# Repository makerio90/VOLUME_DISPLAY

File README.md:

# VOLUME_DISPLAY
this is a project i have been working on for the better part of a month now, this is only the first commit as i have dicided to add the project to github.

## The Idea:
i wanted to make a volumetric pov display. i got insperation from these projects:

- [this project is what kicked it off](https://hackaday.com/2024/09/09/doom-on-a-volumetric-display/)
- [and this served as insperation](https://hackaday.com/2021/02/21/volumetric-3d-television-is-here/)

both work off of the same principle: phisicly rotating an led matrix to create the sense of volume.

this seemed doable so i started work on schematics.

## theory of operation
cutting to the chase here: this is what the mainboard needs to do:

the main board is intended to drive a 32x16 led matrix at a high framerate (>1000fps).
new frames will be added to a framebuffer through a rs-485 bus. 12v power will also be supplied.
a hall effect sensor will provide a sync signal, allowing the board to make minor ajustments to its framerate.
most importently, this whole board rotates around. 12v and rs485 is fed through a slipring.

the entire board must be slowed to a stop in order for the rp2040 to be programmed.
whenever the usb port is plugged in. the rp2040 will be powered and in prog mode.
*the led drivers should be off when usb is plugged in!*

the board will be in the shape of a circle. the led matrix will be mounted vertically in the center via the attached pinheders.
because the board will likely be unbalanced, nuts and bolts will be added around in a circle to provide an option for balance.

## 4-layer stackup

top: high speed traces
in 1: signal, power & ground
in 2: Ground only
BOT: low speed, high current traces.

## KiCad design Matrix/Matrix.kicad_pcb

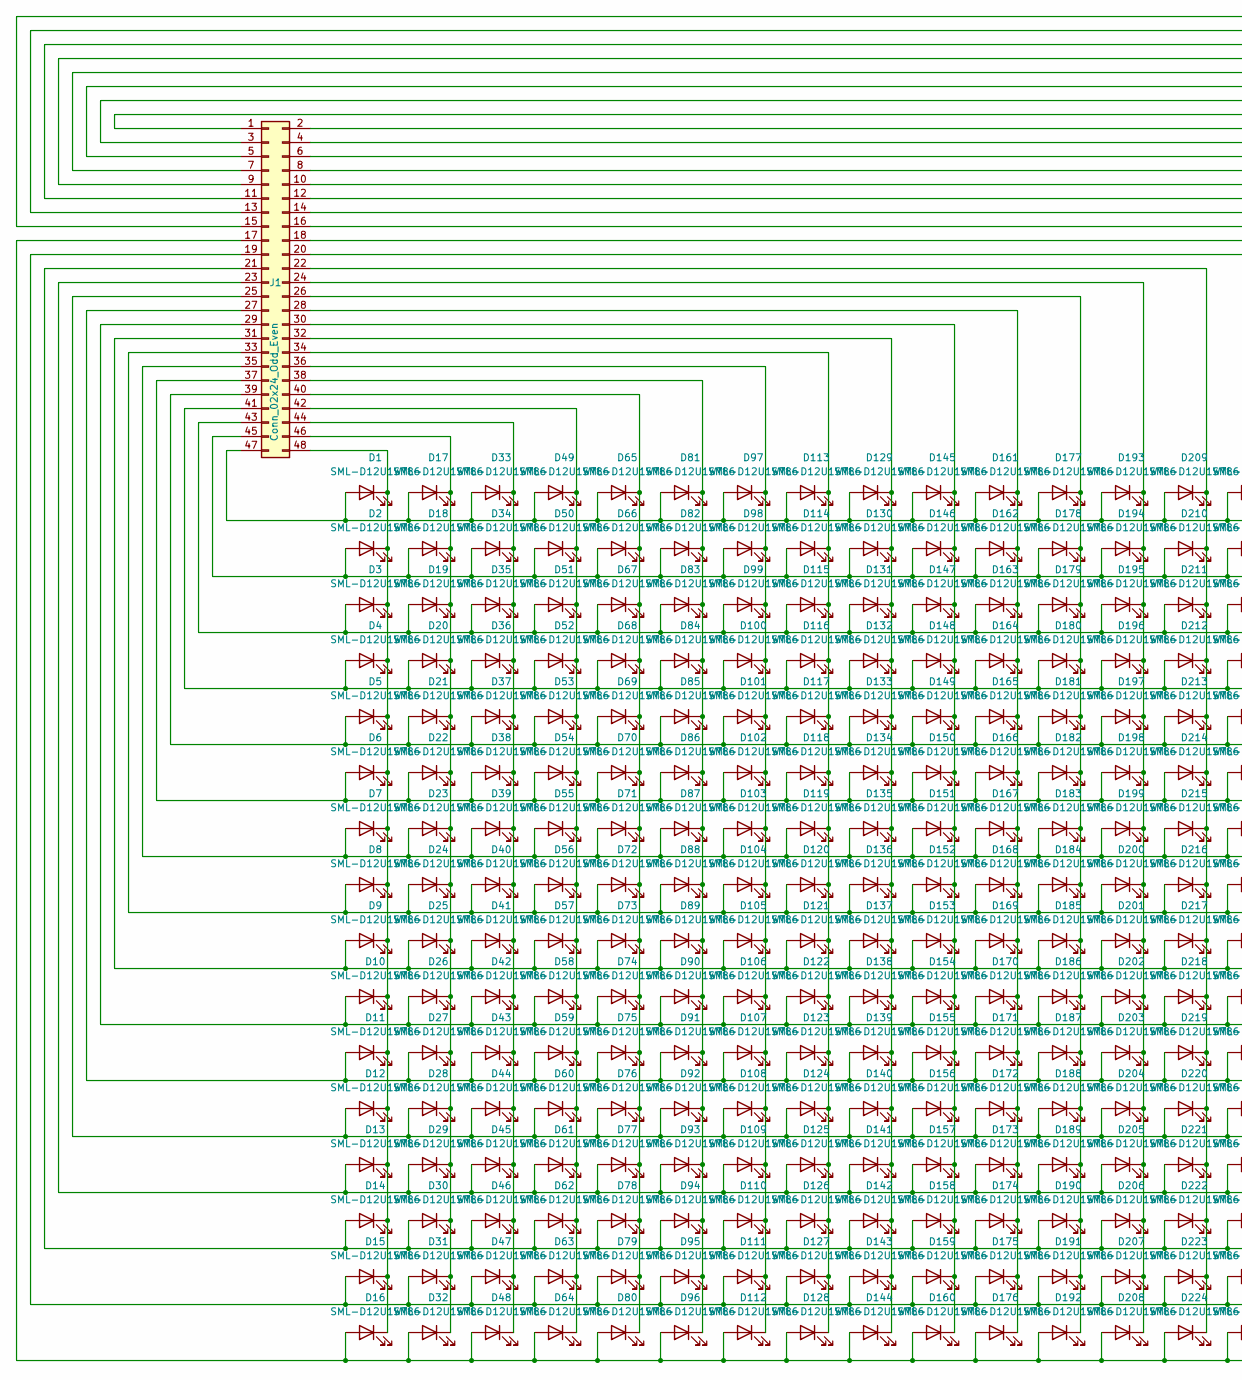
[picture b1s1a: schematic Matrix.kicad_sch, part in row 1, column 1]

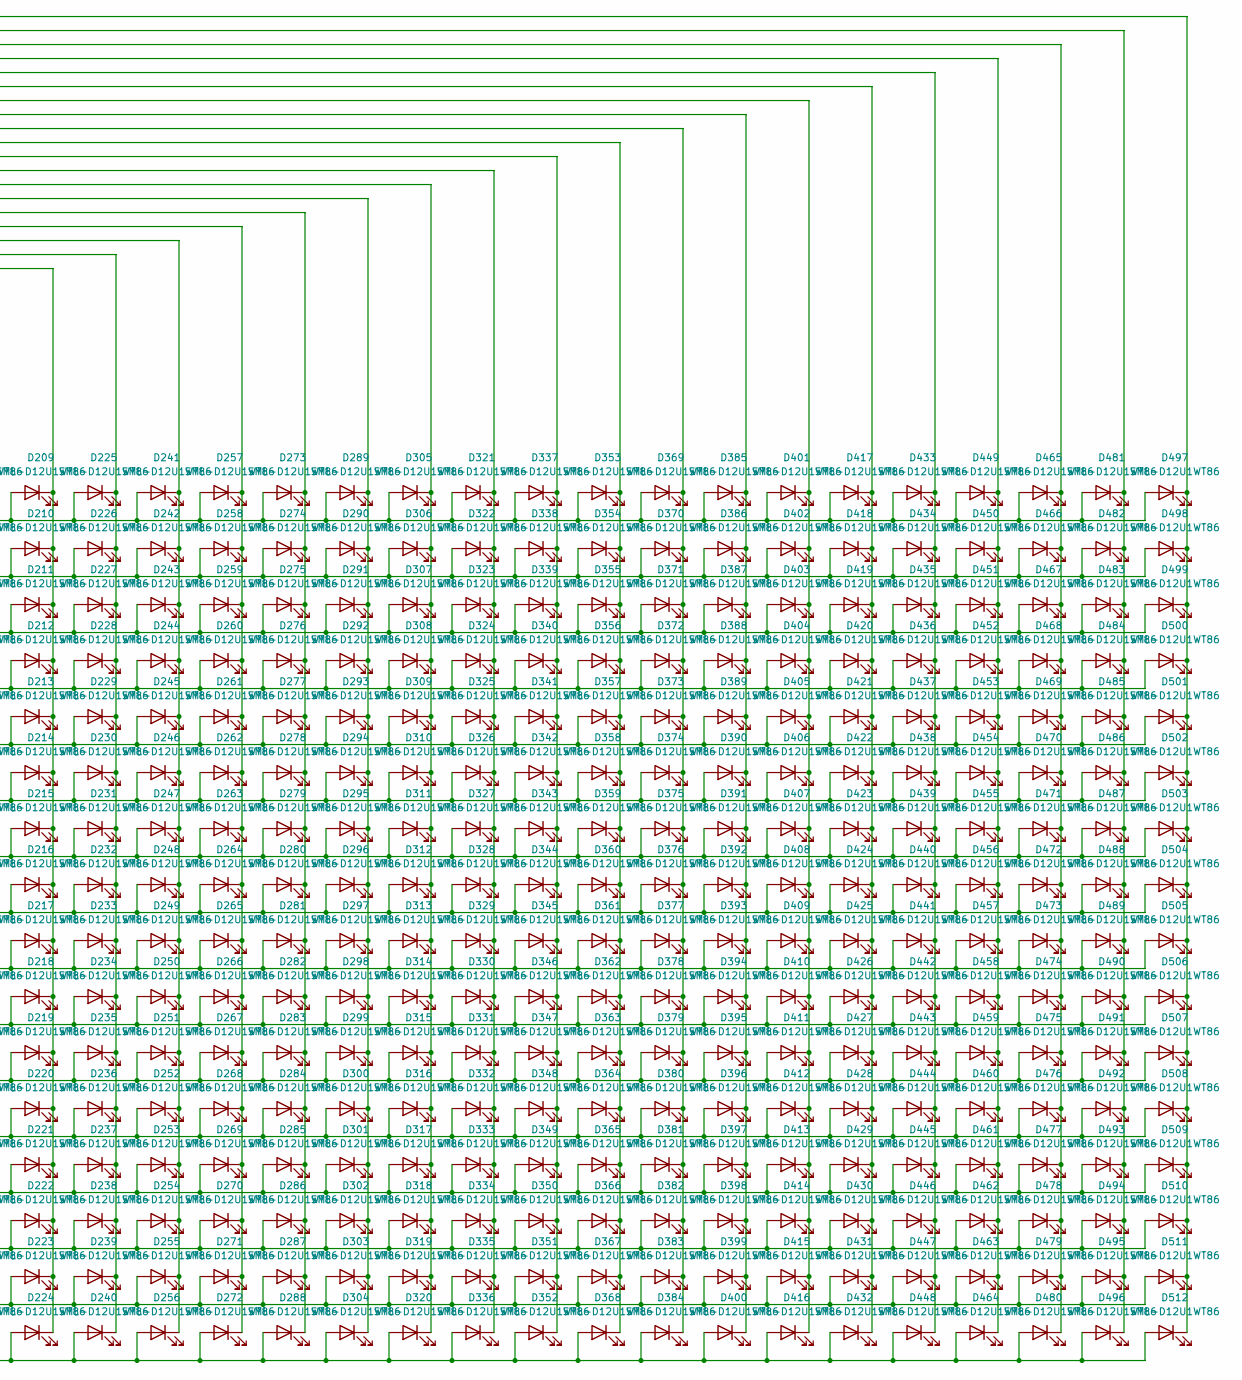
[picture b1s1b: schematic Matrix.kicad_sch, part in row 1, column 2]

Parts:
D1, D2, D3, D4, D5, D6, D7, D8, D9, D10, D11, D12, D13, D14, D15, D16, D17, D18, D19, D20, D21, D22, D23, D24, D25, D26, D27, D28, D29, D30, D31, D32, D33, D34, D35, D36, D37, D38, D39, D40, D41, D42, D43, D44, D45, D46, D47, D48, D49, D50, D51, D52, D53, D54, D55, D56, D57, D58, D59, D60, D61, D62, D63, D64, D65, D66, D67, D68, D69, D70, D71, D72, D73, D74, D75, D76, D77, D78, D79, D80, D81, D82, D83, D84, D85, D86, D87, D88, D89, D90, D91, D92, D93, D94, D95, D96, D97, D98, D99, D100, D101, D102, D103, D104, D105, D106, D107, D108, D109, D110, D111, D112, D113, D114, D115, D116, D117, D118, D119, D120, D121, D122, D123, D124, D125, D126, D127, D128, D129, D130, D131, D132, D133, D134, D135, D136, D137, D138, D139, D140, D141, D142, D143, D144, D145, D146, D147, D148, D149, D150, D151, D152, D153, D154, D155, D156, D157, D158, D159, D160, D161, D162, D163, D164, D165, D166, D167, D168, D169, D170, D171, D172, D173, D174, D175, D176, D177, D178, D179, D180, D181, D182, D183, D184, D185, D186, D187, D188, D189, D190, D191, D192, D193, D194, D195, D196, D197, D198, D199, D200, D201, D202, D203, D204, D205, D206, D207, D208, D209, D210, D211, D212, D213, D214, D215, D216, D217, D218, D219, D220, D221, D222, D223, D224, D225, D226, D227, D228, D229, D230, D231, D232, D233, D234, D235, D236, D237, D238, D239, D240, D241, D242, D243, D244, D245, D246, D247, D248, D249, D250, D251, D252, D253, D254, D255, D256, D257, D258, D259, D260, D261, D262, D263, D264, D265, D266, D267, D268, D269, D270, D271, D272, D273, D274, D275, D276, D277, D278, D279, D280, D281, D282, D283, D284, D285, D286, D287, D288, D289, D290, D291, D292, D293, D294, D295, D296, D297, D298, D299, D300, D301, D302, D303, D304, D305, D306, D307, D308, D309, D310, D311, D312, D313, D314, D315, D316, D317, D318, D319, D320, D321, D322, D323, D324, D325, D326, D327, D328, D329, D330, D331, D332, D333, D334, D335, D336, D337, D338, D339, D340, D341, D342, D343, D344, D345, D346, D347, D348, D349, D350, D351, D352, D353, D354, D355, D356, D357, D358, D359, D360, D361, D362, D363, D364, D365, D366, D367, D368, D369, D370, D371, D372, D373, D374, D375, D376, D377, D378, D379, D380, D381, D382, D383, D384, D385, D386, D387, D388, D389, D390, D391, D392, D393, D394, D395, D396, D397, D398, D399, D400, D401, D402, D403, D404, D405, D406, D407, D408, D409, D410, D411, D412, D413, D414, D415, D416, D417, D418, D419, D420, D421, D422, D423, D424, D425, D426, D427, D428, D429, D430, D431, D432, D433, D434, D435, D436, D437, D438, D439, D440, D441, D442, D443, D444, D445, D446, D447, D448, D449, D450, D451, D452, D453, D454, D455, D456, D457, D458, D459, D460, D461, D462, D463, D464, D465, D466, D467, D468, D469, D470, D471, D472, D473, D474, D475, D476, D477, D478, D479, D480, D481, D482, D483, D484, D485, D486, D487, D488, D489, D490, D491, D492, D493, D494, D495, D496, D497, D498, D499, D500, D501, D502, D503, D504, D505, D506, D507, D508, D509, D510, D511, D512: SML-D12U1WT86; LED_0603_1608Metric
J1: Conn_02x24_Odd_Even; PinHeader_2x24_P2.54mm_Horizontal

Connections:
unnamed: D1.2 (A), D17.2 (A), D33.2 (A), D49.2 (A), D65.2 (A), D81.2 (A), D97.2 (A), D113.2 (A), D129.2 (A), D145.2 (A), D161.2 (A), D177.2 (A), D193.2 (A), D209.2 (A), D225.2 (A), D241.2 (A), D257.2 (A), D273.2 (A), D289.2 (A), D305.2 (A), D321.2 (A), D337.2 (A), D353.2 (A), D369.2 (A), D385.2 (A), D401.2 (A), D417.2 (A), D433.2 (A), D449.2 (A), D465.2 (A), D481.2 (A), D497.2 (A), J1.47
unnamed: D1.1 (K), D2.1 (K), D3.1 (K), D4.1 (K), D5.1 (K), D6.1 (K), D7.1 (K), D8.1 (K), D9.1 (K), D10.1 (K), D11.1 (K), D12.1 (K), D13.1 (K), D14.1 (K), D15.1 (K), D16.1 (K), J1.48
unnamed: D10.2 (A), D26.2 (A), D42.2 (A), D58.2 (A), D74.2 (A), D90.2 (A), D106.2 (A), D122.2 (A), D138.2 (A), D154.2 (A), D170.2 (A), D186.2 (A), D202.2 (A), D218.2 (A), D234.2 (A), D250.2 (A), D266.2 (A), D282.2 (A), D298.2 (A), D314.2 (A), D330.2 (A), D346.2 (A), D362.2 (A), D378.2 (A), D394.2 (A), D410.2 (A), D426.2 (A), D442.2 (A), D458.2 (A), D474.2 (A), D490.2 (A), D506.2 (A), J1.29
unnamed: D17.1 (K), D18.1 (K), D19.1 (K), D20.1 (K), D21.1 (K), D22.1 (K), D23.1 (K), D24.1 (K), D25.1 (K), D26.1 (K), D27.1 (K), D28.1 (K), D29.1 (K), D30.1 (K), D31.1 (K), D32.1 (K), J1.46
unnamed: D33.1 (K), D34.1 (K), D35.1 (K), D36.1 (K), D37.1 (K), D38.1 (K), D39.1 (K), D40.1 (K), D41.1 (K), D42.1 (K), D43.1 (K), D44.1 (K), D45.1 (K), D46.1 (K), D47.1 (K), D48.1 (K), J1.44
unnamed: D49.1 (K), D50.1 (K), D51.1 (K), D52.1 (K), D53.1 (K), D54.1 (K), D55.1 (K), D56.1 (K), D57.1 (K), D58.1 (K), D59.1 (K), D60.1 (K), D61.1 (K), D62.1 (K), D63.1 (K), D64.1 (K), J1.42
unnamed: D65.1 (K), D66.1 (K), D67.1 (K), D68.1 (K), D69.1 (K), D70.1 (K), D71.1 (K), D72.1 (K), D73.1 (K), D74.1 (K), D75.1 (K), D76.1 (K), D77.1 (K), D78.1 (K), D79.1 (K), D80.1 (K), J1.40
unnamed: D81.1 (K), D82.1 (K), D83.1 (K), D84.1 (K), D85.1 (K), D86.1 (K), D87.1 (K), D88.1 (K), D89.1 (K), D90.1 (K), D91.1 (K), D92.1 (K), D93.1 (K), D94.1 (K), D95.1 (K), D96.1 (K), J1.38
unnamed: D4.2 (A), D20.2 (A), D36.2 (A), D52.2 (A), D68.2 (A), D84.2 (A), D100.2 (A), D116.2 (A), D132.2 (A), D148.2 (A), D164.2 (A), D180.2 (A), D196.2 (A), D212.2 (A), D228.2 (A), D244.2 (A), D260.2 (A), D276.2 (A), D292.2 (A), D308.2 (A), D324.2 (A), D340.2 (A), D356.2 (A), D372.2 (A), D388.2 (A), D404.2 (A), D420.2 (A), D436.2 (A), D452.2 (A), D468.2 (A), D484.2 (A), D500.2 (A), J1.41
unnamed: D97.1 (K), D98.1 (K), D99.1 (K), D100.1 (K), D101.1 (K), D102.1 (K), D103.1 (K), D104.1 (K), D105.1 (K), D106.1 (K), D107.1 (K), D108.1 (K), D109.1 (K), D110.1 (K), D111.1 (K), D112.1 (K), J1.36
unnamed: D5.2 (A), D21.2 (A), D37.2 (A), D53.2 (A), D69.2 (A), D85.2 (A), D101.2 (A), D117.2 (A), D133.2 (A), D149.2 (A), D165.2 (A), D181.2 (A), D197.2 (A), D213.2 (A), D229.2 (A), D245.2 (A), D261.2 (A), D277.2 (A), D293.2 (A), D309.2 (A), D325.2 (A), D341.2 (A), D357.2 (A), D373.2 (A), D389.2 (A), D405.2 (A), D421.2 (A), D437.2 (A), D453.2 (A), D469.2 (A), D485.2 (A), D501.2 (A), J1.39
unnamed: D6.2 (A), D22.2 (A), D38.2 (A), D54.2 (A), D70.2 (A), D86.2 (A), D102.2 (A), D118.2 (A), D134.2 (A), D150.2 (A), D166.2 (A), D182.2 (A), D198.2 (A), D214.2 (A), D230.2 (A), D246.2 (A), D262.2 (A), D278.2 (A), D294.2 (A), D310.2 (A), D326.2 (A), D342.2 (A), D358.2 (A), D374.2 (A), D390.2 (A), D406.2 (A), D422.2 (A), D438.2 (A), D454.2 (A), D470.2 (A), D486.2 (A), D502.2 (A), J1.37
unnamed: D7.2 (A), D23.2 (A), D39.2 (A), D55.2 (A), D71.2 (A), D87.2 (A), D103.2 (A), D119.2 (A), D135.2 (A), D151.2 (A), D167.2 (A), D183.2 (A), D199.2 (A), D215.2 (A), D231.2 (A), D247.2 (A), D263.2 (A), D279.2 (A), D295.2 (A), D311.2 (A), D327.2 (A), D343.2 (A), D359.2 (A), D375.2 (A), D391.2 (A), D407.2 (A), D423.2 (A), D439.2 (A), D455.2 (A), D471.2 (A), D487.2 (A), D503.2 (A), J1.35
unnamed: D8.2 (A), D24.2 (A), D40.2 (A), D56.2 (A), D72.2 (A), D88.2 (A), D104.2 (A), D120.2 (A), D136.2 (A), D152.2 (A), D168.2 (A), D184.2 (A), D200.2 (A), D216.2 (A), D232.2 (A), D248.2 (A), D264.2 (A), D280.2 (A), D296.2 (A), D312.2 (A), D328.2 (A), D344.2 (A), D360.2 (A), D376.2 (A), D392.2 (A), D408.2 (A), D424.2 (A), D440.2 (A), D456.2 (A), D472.2 (A), D488.2 (A), D504.2 (A), J1.33
unnamed: D9.2 (A), D25.2 (A), D41.2 (A), D57.2 (A), D73.2 (A), D89.2 (A), D105.2 (A), D121.2 (A), D137.2 (A), D153.2 (A), D169.2 (A), D185.2 (A), D201.2 (A), D217.2 (A), D233.2 (A), D249.2 (A), D265.2 (A), D281.2 (A), D297.2 (A), D313.2 (A), D329.2 (A), D345.2 (A), D361.2 (A), D377.2 (A), D393.2 (A), D409.2 (A), D425.2 (A), D441.2 (A), D457.2 (A), D473.2 (A), D489.2 (A), D505.2 (A), J1.31
unnamed: D11.2 (A), D27.2 (A), D43.2 (A), D59.2 (A), D75.2 (A), D91.2 (A), D107.2 (A), D123.2 (A), D139.2 (A), D155.2 (A), D171.2 (A), D187.2 (A), D203.2 (A), D219.2 (A), D235.2 (A), D251.2 (A), D267.2 (A), D283.2 (A), D299.2 (A), D315.2 (A), D331.2 (A), D347.2 (A), D363.2 (A), D379.2 (A), D395.2 (A), D411.2 (A), D427.2 (A), D443.2 (A), D459.2 (A), D475.2 (A), D491.2 (A), D507.2 (A), J1.27
unnamed: D12.2 (A), D28.2 (A), D44.2 (A), D60.2 (A), D76.2 (A), D92.2 (A), D108.2 (A), D124.2 (A), D140.2 (A), D156.2 (A), D172.2 (A), D188.2 (A), D204.2 (A), D220.2 (A), D236.2 (A), D252.2 (A), D268.2 (A), D284.2 (A), D300.2 (A), D316.2 (A), D332.2 (A), D348.2 (A), D364.2 (A), D380.2 (A), D396.2 (A), D412.2 (A), D428.2 (A), D444.2 (A), D460.2 (A), D476.2 (A), D492.2 (A), D508.2 (A), J1.25
unnamed: D13.2 (A), D29.2 (A), D45.2 (A), D61.2 (A), D77.2 (A), D93.2 (A), D109.2 (A), D125.2 (A), D141.2 (A), D157.2 (A), D173.2 (A), D189.2 (A), D205.2 (A), D221.2 (A), D237.2 (A), D253.2 (A), D269.2 (A), D285.2 (A), D301.2 (A), D317.2 (A), D333.2 (A), D349.2 (A), D365.2 (A), D381.2 (A), D397.2 (A), D413.2 (A), D429.2 (A), D445.2 (A), D461.2 (A), D477.2 (A), D493.2 (A), D509.2 (A), J1.23
unnamed: D14.2 (A), D30.2 (A), D46.2 (A), D62.2 (A), D78.2 (A), D94.2 (A), D110.2 (A), D126.2 (A), D142.2 (A), D158.2 (A), D174.2 (A), D190.2 (A), D206.2 (A), D222.2 (A), D238.2 (A), D254.2 (A), D270.2 (A), D286.2 (A), D302.2 (A), D318.2 (A), D334.2 (A), D350.2 (A), D366.2 (A), D382.2 (A), D398.2 (A), D414.2 (A), D430.2 (A), D446.2 (A), D462.2 (A), D478.2 (A), D494.2 (A), D510.2 (A), J1.21
unnamed: D15.2 (A), D31.2 (A), D47.2 (A), D63.2 (A), D79.2 (A), D95.2 (A), D111.2 (A), D127.2 (A), D143.2 (A), D159.2 (A), D175.2 (A), D191.2 (A), D207.2 (A), D223.2 (A), D239.2 (A), D255.2 (A), D271.2 (A), D287.2 (A), D303.2 (A), D319.2 (A), D335.2 (A), D351.2 (A), D367.2 (A), D383.2 (A), D399.2 (A), D415.2 (A), D431.2 (A), D447.2 (A), D463.2 (A), D479.2 (A), D495.2 (A), D511.2 (A), J1.19
unnamed: D16.2 (A), D32.2 (A), D48.2 (A), D64.2 (A), D80.2 (A), D96.2 (A), D112.2 (A), D128.2 (A), D144.2 (A), D160.2 (A), D176.2 (A), D192.2 (A), D208.2 (A), D224.2 (A), D240.2 (A), D256.2 (A), D272.2 (A), D288.2 (A), D304.2 (A), D320.2 (A), D336.2 (A), D352.2 (A), D368.2 (A), D384.2 (A), D400.2 (A), D416.2 (A), D432.2 (A), D448.2 (A), D464.2 (A), D480.2 (A), D496.2 (A), D512.2 (A), J1.17
unnamed: D113.1 (K), D114.1 (K), D115.1 (K), D116.1 (K), D117.1 (K), D118.1 (K), D119.1 (K), D120.1 (K), D121.1 (K), D122.1 (K), D123.1 (K), D124.1 (K), D125.1 (K), D126.1 (K), D127.1 (K), D128.1 (K), J1.34
unnamed: D2.2 (A), D18.2 (A), D34.2 (A), D50.2 (A), D66.2 (A), D82.2 (A), D98.2 (A), D114.2 (A), D130.2 (A), D146.2 (A), D162.2 (A), D178.2 (A), D194.2 (A), D210.2 (A), D226.2 (A), D242.2 (A), D258.2 (A), D274.2 (A), D290.2 (A), D306.2 (A), D322.2 (A), D338.2 (A), D354.2 (A), D370.2 (A), D386.2 (A), D402.2 (A), D418.2 (A), D434.2 (A), D450.2 (A), D466.2 (A), D482.2 (A), D498.2 (A), J1.45
unnamed: D3.2 (A), D19.2 (A), D35.2 (A), D51.2 (A), D67.2 (A), D83.2 (A), D99.2 (A), D115.2 (A), D131.2 (A), D147.2 (A), D163.2 (A), D179.2 (A), D195.2 (A), D211.2 (A), D227.2 (A), D243.2 (A), D259.2 (A), D275.2 (A), D291.2 (A), D307.2 (A), D323.2 (A), D339.2 (A), D355.2 (A), D371.2 (A), D387.2 (A), D403.2 (A), D419.2 (A), D435.2 (A), D451.2 (A), D467.2 (A), D483.2 (A), D499.2 (A), J1.43
unnamed: D129.1 (K), D130.1 (K), D131.1 (K), D132.1 (K), D133.1 (K), D134.1 (K), D135.1 (K), D136.1 (K), D137.1 (K), D138.1 (K), D139.1 (K), D140.1 (K), D141.1 (K), D142.1 (K), D143.1 (K), D144.1 (K), J1.32
unnamed: D145.1 (K), D146.1 (K), D147.1 (K), D148.1 (K), D149.1 (K), D150.1 (K), D151.1 (K), D152.1 (K), D153.1 (K), D154.1 (K), D155.1 (K), D156.1 (K), D157.1 (K), D158.1 (K), D159.1 (K), D160.1 (K), J1.30
unnamed: D161.1 (K), D162.1 (K), D163.1 (K), D164.1 (K), D165.1 (K), D166.1 (K), D167.1 (K), D168.1 (K), D169.1 (K), D170.1 (K), D171.1 (K), D172.1 (K), D173.1 (K), D174.1 (K), D175.1 (K), D176.1 (K), J1.28
unnamed: D177.1 (K), D178.1 (K), D179.1 (K), D180.1 (K), D181.1 (K), D182.1 (K), D183.1 (K), D184.1 (K), D185.1 (K), D186.1 (K), D187.1 (K), D188.1 (K), D189.1 (K), D190.1 (K), D191.1 (K), D192.1 (K), J1.26
unnamed: D193.1 (K), D194.1 (K), D195.1 (K), D196.1 (K), D197.1 (K), D198.1 (K), D199.1 (K), D200.1 (K), D201.1 (K), D202.1 (K), D203.1 (K), D204.1 (K), D205.1 (K), D206.1 (K), D207.1 (K), D208.1 (K), J1.24
unnamed: D209.1 (K), D210.1 (K), D211.1 (K), D212.1 (K), D213.1 (K), D214.1 (K), D215.1 (K), D216.1 (K), D217.1 (K), D218.1 (K), D219.1 (K), D220.1 (K), D221.1 (K), D222.1 (K), D223.1 (K), D224.1 (K), J1.22
unnamed: D225.1 (K), D226.1 (K), D227.1 (K), D228.1 (K), D229.1 (K), D230.1 (K), D231.1 (K), D232.1 (K), D233.1 (K), D234.1 (K), D235.1 (K), D236.1 (K), D237.1 (K), D238.1 (K), D239.1 (K), D240.1 (K), J1.20
unnamed: D241.1 (K), D242.1 (K), D243.1 (K), D244.1 (K), D245.1 (K), D246.1 (K), D247.1 (K), D248.1 (K), D249.1 (K), D250.1 (K), D251.1 (K), D252.1 (K), D253.1 (K), D254.1 (K), D255.1 (K), D256.1 (K), J1.18
unnamed: D257.1 (K), D258.1 (K), D259.1 (K), D260.1 (K), D261.1 (K), D262.1 (K), D263.1 (K), D264.1 (K), D265.1 (K), D266.1 (K), D267.1 (K), D268.1 (K), D269.1 (K), D270.1 (K), D271.1 (K), D272.1 (K), J1.16
unnamed: D273.1 (K), D274.1 (K), D275.1 (K), D276.1 (K), D277.1 (K), D278.1 (K), D279.1 (K), D280.1 (K), D281.1 (K), D282.1 (K), D283.1 (K), D284.1 (K), D285.1 (K), D286.1 (K), D287.1 (K), D288.1 (K), J1.14
unnamed: D289.1 (K), D290.1 (K), D291.1 (K), D292.1 (K), D293.1 (K), D294.1 (K), D295.1 (K), D296.1 (K), D297.1 (K), D298.1 (K), D299.1 (K), D300.1 (K), D301.1 (K), D302.1 (K), D303.1 (K), D304.1 (K), J1.12
unnamed: D305.1 (K), D306.1 (K), D307.1 (K), D308.1 (K), D309.1 (K), D310.1 (K), D311.1 (K), D312.1 (K), D313.1 (K), D314.1 (K), D315.1 (K), D316.1 (K), D317.1 (K), D318.1 (K), D319.1 (K), D320.1 (K), J1.10
unnamed: D321.1 (K), D322.1 (K), D323.1 (K), D324.1 (K), D325.1 (K), D326.1 (K), D327.1 (K), D328.1 (K), D329.1 (K), D330.1 (K), D331.1 (K), D332.1 (K), D333.1 (K), D334.1 (K), D335.1 (K), D336.1 (K), J1.8
unnamed: D337.1 (K), D338.1 (K), D339.1 (K), D340.1 (K), D341.1 (K), D342.1 (K), D343.1 (K), D344.1 (K), D345.1 (K), D346.1 (K), D347.1 (K), D348.1 (K), D349.1 (K), D350.1 (K), D351.1 (K), D352.1 (K), J1.6
unnamed: D353.1 (K), D354.1 (K), D355.1 (K), D356.1 (K), D357.1 (K), D358.1 (K), D359.1 (K), D360.1 (K), D361.1 (K), D362.1 (K), D363.1 (K), D364.1 (K), D365.1 (K), D366.1 (K), D367.1 (K), D368.1 (K), J1.4
unnamed: D369.1 (K), D370.1 (K), D371.1 (K), D372.1 (K), D373.1 (K), D374.1 (K), D375.1 (K), D376.1 (K), D377.1 (K), D378.1 (K), D379.1 (K), D380.1 (K), D381.1 (K), D382.1 (K), D383.1 (K), D384.1 (K), J1.2
unnamed: D385.1 (K), D386.1 (K), D387.1 (K), D388.1 (K), D389.1 (K), D390.1 (K), D391.1 (K), D392.1 (K), D393.1 (K), D394.1 (K), D395.1 (K), D396.1 (K), D397.1 (K), D398.1 (K), D399.1 (K), D400.1 (K), J1.1
unnamed: D401.1 (K), D402.1 (K), D403.1 (K), D404.1 (K), D405.1 (K), D406.1 (K), D407.1 (K), D408.1 (K), D409.1 (K), D410.1 (K), D411.1 (K), D412.1 (K), D413.1 (K), D414.1 (K), D415.1 (K), D416.1 (K), J1.3
unnamed: D417.1 (K), D418.1 (K), D419.1 (K), D420.1 (K), D421.1 (K), D422.1 (K), D423.1 (K), D424.1 (K), D425.1 (K), D426.1 (K), D427.1 (K), D428.1 (K), D429.1 (K), D430.1 (K), D431.1 (K), D432.1 (K), J1.5
unnamed: D433.1 (K), D434.1 (K), D435.1 (K), D436.1 (K), D437.1 (K), D438.1 (K), D439.1 (K), D440.1 (K), D441.1 (K), D442.1 (K), D443.1 (K), D444.1 (K), D445.1 (K), D446.1 (K), D447.1 (K), D448.1 (K), J1.7
unnamed: D449.1 (K), D450.1 (K), D451.1 (K), D452.1 (K), D453.1 (K), D454.1 (K), D455.1 (K), D456.1 (K), D457.1 (K), D458.1 (K), D459.1 (K), D460.1 (K), D461.1 (K), D462.1 (K), D463.1 (K), D464.1 (K), J1.9
unnamed: D465.1 (K), D466.1 (K), D467.1 (K), D468.1 (K), D469.1 (K), D470.1 (K), D471.1 (K), D472.1 (K), D473.1 (K), D474.1 (K), D475.1 (K), D476.1 (K), D477.1 (K), D478.1 (K), D479.1 (K), D480.1 (K), J1.11
unnamed: D481.1 (K), D482.1 (K), D483.1 (K), D484.1 (K), D485.1 (K), D486.1 (K), D487.1 (K), D488.1 (K), D489.1 (K), D490.1 (K), D491.1 (K), D492.1 (K), D493.1 (K), D494.1 (K), D495.1 (K), D496.1 (K), J1.13
unnamed: D497.1 (K), D498.1 (K), D499.1 (K), D500.1 (K), D501.1 (K), D502.1 (K), D503.1 (K), D504.1 (K), D505.1 (K), D506.1 (K), D507.1 (K), D508.1 (K), D509.1 (K), D510.1 (K), D511.1 (K), D512.1 (K), J1.15

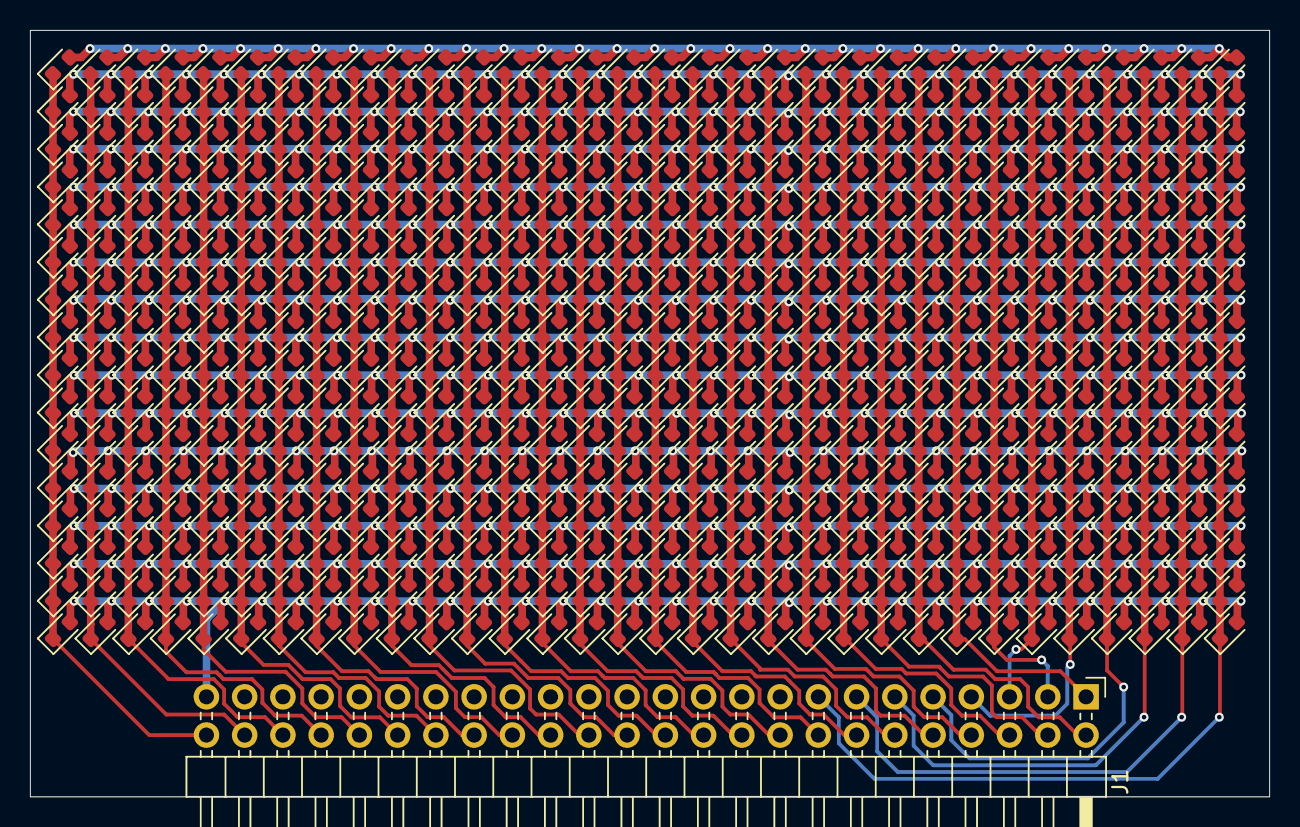
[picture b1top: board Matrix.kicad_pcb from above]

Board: 4 copper layers, 82.3 x 50.9 mm, 513 parts (0 on the bottom side), 48 nets.

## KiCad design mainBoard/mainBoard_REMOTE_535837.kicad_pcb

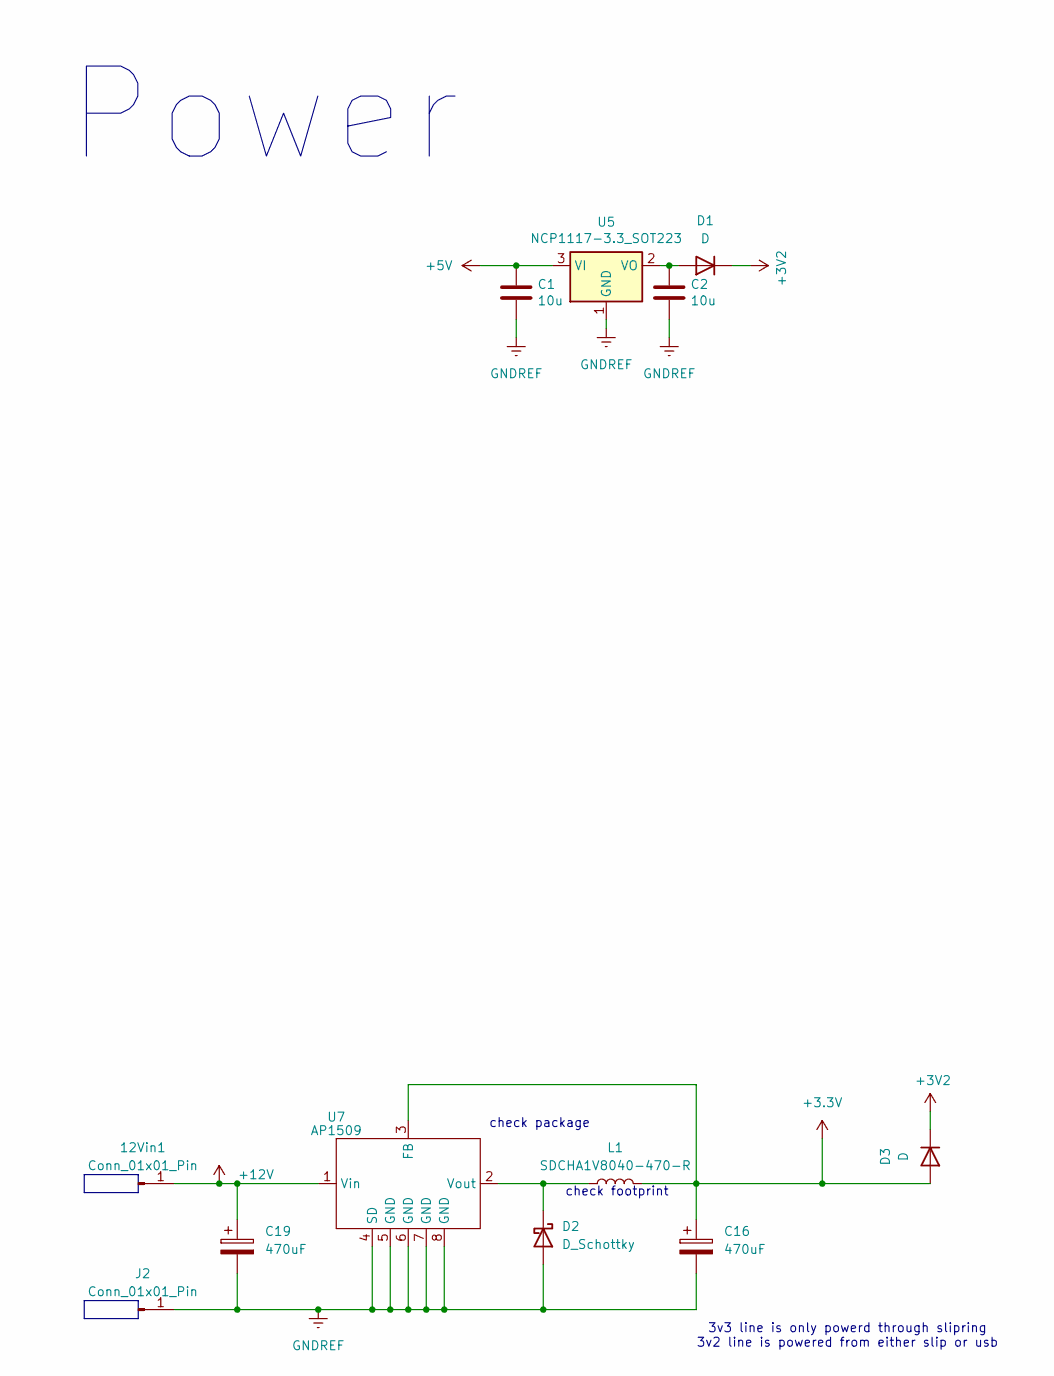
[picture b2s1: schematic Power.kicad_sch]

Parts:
12Vin1: Conn_01x01_Pin; PinHeader_1x01_P2.54mm_Vertical
C1, C2: 10u; C_0805_2012Metric; MPN CL21A106KAYNNNE; LCSC PN C15850
C16, C19: 470uF; C_Elec_8x10.2; MPN EEEFP1C471AP; LCSC PN C343909
D1, D3: D; D_0402_1005Metric; MPN LQW15AN12NH00D; LCSC PN C703125
D2: D_Schottky; D_SMB; MPN TPNSR05F40NXT5G; LCSC PN C28642302
J2: Conn_01x01_Pin; PinHeader_1x01_P2.54mm_Vertical
L1: SDCHA1V8040-470-R; L_Coilcraft_XAL8080-XXX; MPN SDCHA1V8040-470-R; LCSC PN C17221881
U5: NCP1117-3.3_SOT223; SOT-223-3_TabPin2; MPN NCP1117ST12T3G; LCSC PN C98965
U7: AP1509; SOP-8_5.28x5.23mm_P1.27mm; MPN AP1509-SG-13; LCSC PN C151822

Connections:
+3.3V: C16.1, D3.2 (A), L1.2, U7.3 (FB); also elsewhere on the board
+3V2: D1.1 (K), D3.1 (K); also elsewhere on the board
+5V: C1.1, U5.3 (VI); also elsewhere on the board
+12V: 12Vin1.1, C19.1, U7.1 (Vin)
GNDREF: C1.2, C2.2, C16.2, C19.2, D2.2 (A), J2.1, U5.1 (GND), U7.4 (SD), U7.5 (GND), U7.6 (GND), U7.7 (GND), U7.8 (GND); also elsewhere on the board
unnamed: C2.1, D1.2 (A), U5.2 (VO)
unnamed: D2.1 (K), L1.1, U7.2 (Vout)

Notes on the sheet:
check package
Power
check footprint
3v3 line is only powerd through slipring 3v2 line is powered from either slip or usb
